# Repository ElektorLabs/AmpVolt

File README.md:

# AmpVolt: VI Measurement Module - 240141 📊

## Overview 🌐
AmpVolt, designed for the any Arduino or ESP32 project, is a  module for accurately measuring current and voltage with ease. Featuring a voltage divider, INA169 for current sensing, and an ADS1015 ADC, it's equipped with an OLED display for immediate feedback. Suitable for electrical projects requiring up to 50V and 5A measurements, it offers modular connectivity through Grove, Qwiic, and 2.54mm pitch connectors.

## Key Features 🚀
- Precise current and voltage measurement up to 50V and 5A.
- Modular design with Grove, Qwiic, and standard connectors.
- Real-time data display on an OLED screen.
- Tested on ESP32-C3 Mini.

## Hardware Design 🛠️
AmpVolt's PCB is designed for flexibility, featuring various connectors to suit diverse project needs. The inclusion of Grove and Qwiic connectors alongside traditional 2.54mm pitch options ensures compatibility with a wide range of devices and systems.

## Function Descriptions 📖

### `setup()`
Initializes the system: sets up serial communication, I2C parameters, ADC gain, and data rate for quick measurements, and checks the OLED display's status.

### `loop()`
Main program loop: periodically reads commands, updates measurements, calculates energy consumed, and refreshes the OLED display with current data.

### `readVoltage()`
Reads and calculates the voltage from ADS1115 based on the voltage divider's configuration. It applies corrections for zero error and scales the reading according to the resistive divider ratio.

### `readCurrent()`
Measures the current using the INA169 and ADS1115, adjusting the value with a calibration factor to account for zero error and component variations.

### `calculateAndSendAdditionalData()`
Compiles voltage, current, and calculated power into a comprehensive dataset, including energy consumed and battery state of charge (SoC), then outputs this information through the serial port in JSON format.

### `readCommand()`
Listens for incoming serial commands, assembling them character-by-character until a newline character is encountered, indicating a complete command ready for processing.

### `sendData(String type)`
Responds to specific command types by reading sensor values, performing calculations, and sending the requested data back through the serial port.

### `updateDisplay()`
Refreshes the OLED display with the latest measurement data, including voltage, current, power, elapsed time, battery capacity, energy consumed, and remaining battery percentage.

## Installation & Usage 💡
Follow detailed steps to clone the repo, prepare your microcontroller, assemble the module, and start measuring with the provided Arduino sketch.

## Acknowledgements 🙏
Credits to the creators of the ADS1X15 and Adafruit libraries, enabling the AmpVolt project to utilize advanced ADC and display functionalities.

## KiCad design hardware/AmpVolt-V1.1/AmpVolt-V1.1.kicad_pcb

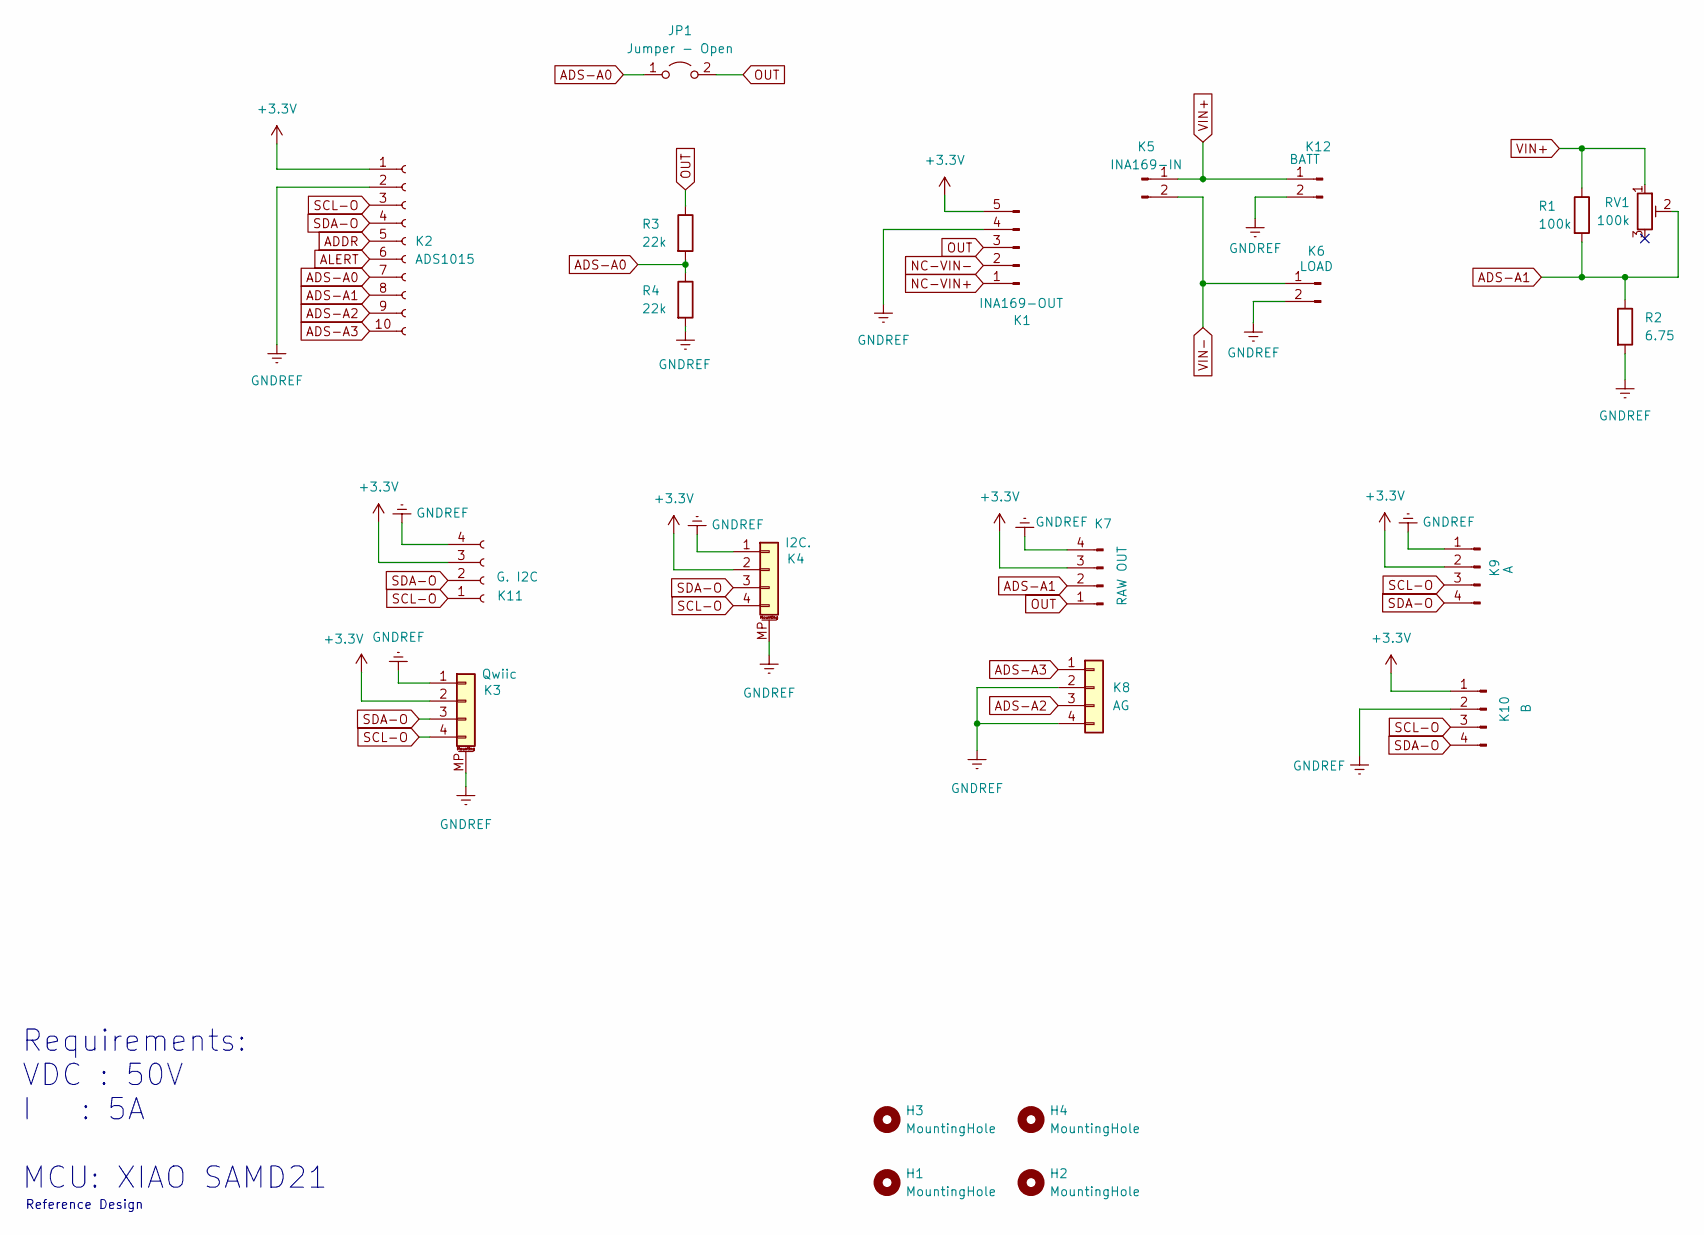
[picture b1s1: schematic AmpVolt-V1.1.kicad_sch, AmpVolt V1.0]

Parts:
H1, H2, H3, H4: MountingHole; MountingHole_3.2mm_M3_DIN965_Pad_TopOnly
JP1: Jumper - Open; SolderJumper-2_P1.3mm_Open_TrianglePad1.0x1.5mm
K1: INA169-OUT; PinSocket_1x05_P2.54mm_Vertical
K2: ADS1015; PinHeader_1x10_P2.54mm_Vertical
K3: Qwiic; JST_SH_SM04B-SRSS-TB_1x04-1MP_P1.00mm_Horizontal
K4: I2C.; JST_PH_S4B-PH-SM4-TB_1x04-1MP_P2.00mm_Horizontal
K5: INA169-IN; PhoenixContact_MCV_1,5_2-G-5.08_1x02_P5.08mm_Vertical
K6: LOAD; AMASS_XT60PW-F_1x02_P7.20mm_Horizontal
K7: RAW OUT; PinHeader_1x04_P2.54mm_Vertical
K8: AG; PinHeader_1x04_P2.54mm_Vertical
K9: A; PinHeader_1x04_P2.54mm_Vertical
K10: B; PinHeader_1x04_P2.54mm_Vertical
K11: G. I2C; JST_EH_S4B-EH_1x04_P2.50mm_Horizontal
K12: BATT; AMASS_XT60PW-F_1x02_P7.20mm_Horizontal
R1: 100k; R_Axial_DIN0204_L3.6mm_D1.6mm_P7.62mm_Horizontal
R2: 6.75; R_Axial_DIN0204_L3.6mm_D1.6mm_P7.62mm_Horizontal
R3, R4: 22k; R_Axial_DIN0204_L3.6mm_D1.6mm_P7.62mm_Horizontal
RV1: 100k; Potentiometer_Bourns_3296W_Vertical

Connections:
+3.3V: K1.5, K2.1, K3.2, K4.2, K7.3, K9.2, K10.1, K11.3
ADDR: K2.5
ADS-A0: JP1.1 (A), K2.7, R3.2, R4.1
ADS-A1: K2.8, K7.2, R1.2, R2.1, RV1.2
ADS-A2: K2.9, K8.3
ADS-A3: K2.10, K8.1
ALERT: K2.6
GNDREF: K1.4, K2.2, K3.1, K3.MP (MountPin), K4.1, K4.MP (MountPin), K6.2, K7.4, K8.2, K8.4, K9.1, K10.2, K11.4, K12.2, R2.2, R4.2
NC-VIN+: K1.1
NC-VIN-: K1.2
OUT: JP1.2 (B), K1.3, K7.1, R3.1
SCL-O: K2.3, K3.4, K4.4, K9.3, K10.3, K11.1
SDA-O: K2.4, K3.3, K4.3, K9.4, K10.4, K11.2
VIN+: K5.1, K12.1, R1.1, RV1.1
VIN-: K5.2, K6.1

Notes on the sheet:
Requirements: VDC : 50V I : 5A MCU: XIAO SAMD21
Reference Design

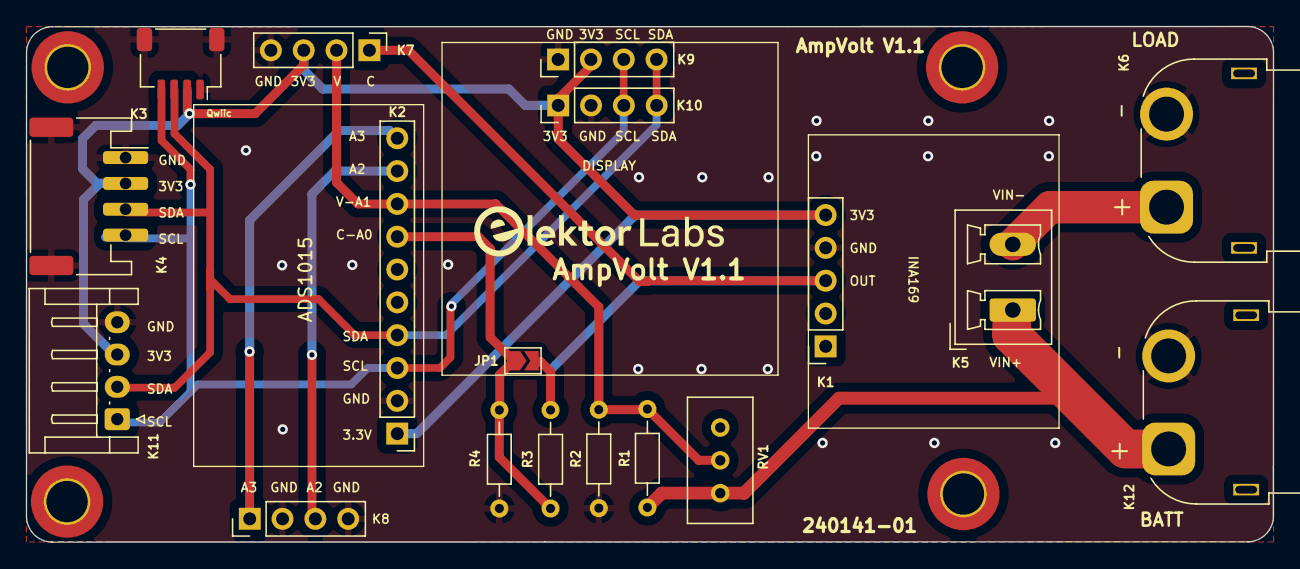
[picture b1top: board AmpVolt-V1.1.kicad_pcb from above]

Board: 2 copper layers, 96.5 x 39.9 mm, 22 parts (0 on the bottom side), 11 nets.

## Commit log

2024-03-22 added files
2024-10-30 v1.1
    What is new ?
    - The PCB Layout is updated, with better mounting points and minor tweaks.
    [The schematic is the not changed]
